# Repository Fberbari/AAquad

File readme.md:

This is an implementation of a quadcopter filght computer running baremetal on an atmega 328pb chip that takes input a standard hobby receiver and outputs pwm to esc's.

These directories contain the full firmware and the pcb design + gerber files.

As of right now, the system produces desirable results and has passed some basic functionality tests. 
I am currently waiting on a mechanical engineering student to finish designing the frame of the aircraft before further testing.

WORKING PRINCIPLE

	As of right now, the system reads input from the receiver via an interrupt based (asynchronous approach). This, because of the 50Hz pwm encoding that the receiver emits is by far the slowest process.

	Apart from this step, the rest of the processis synchronous and the loop goesas follows:

		1. The processor gathers data from the 2 on board sensors (accelerometer and gyroscope) via I2C.
		2. Using a modified version of the Kallman filter, the processor uses both pieces of data to determine the absolute position of the aircraft (with reference to gravity)
		3. A function gathers all the newest available data from the pilot and computes the pilots intention. (How should the aircraft bank and pitch and how strong should 		motor power be)
		4. A PID algorythim then uses the processed sensor data aswell, the processed pilot data and the previous cycle's data to compute 4 numbers that represent the 				percentage of full power that each motor should run at to best achieve the pilot's wishes
		5. Those numbers are encodedinto values that the pwm chip can understand and sent to it via I2C.
		6. The process repeats

PURPOSE

	The purose of this project was to familiarize myself with the basics of avr architecture, firmware design flow, communications between chips (I2C), pcb design flow etc.
	It was also a way to enter the world of embedded design in aviation. 

I (Anthony Berbari) AM SOLELY RESPONSIBLE FOR ALL THE FIRMWARE AND HARDWARE DESIGN DONE ON THIS PROJECT.

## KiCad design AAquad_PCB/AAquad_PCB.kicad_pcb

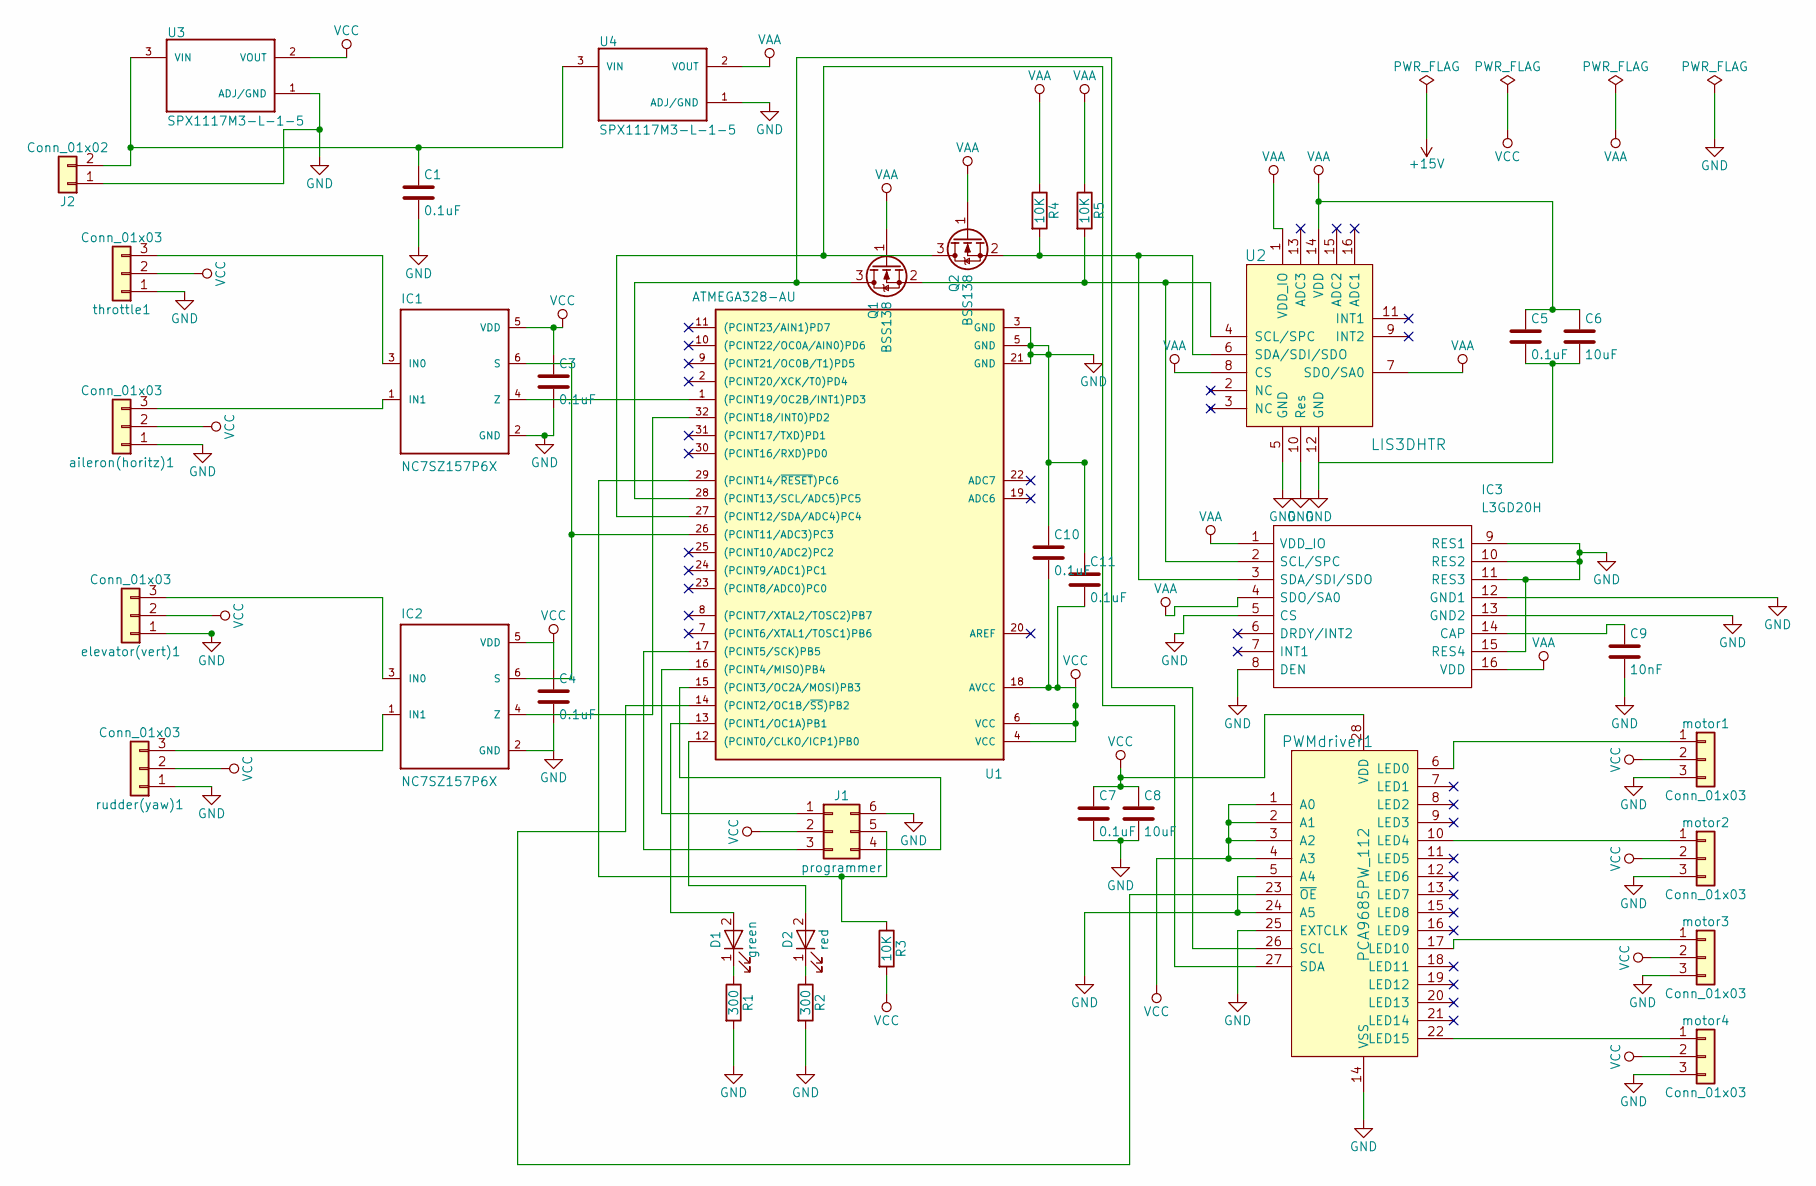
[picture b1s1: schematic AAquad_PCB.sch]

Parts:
C1, C3, C4, C5, C7, C10, C11: 0.1uF; C_0805_HandSoldering
C6, C8: 10uF; C_0805_HandSoldering
C9: 10nF; C_0805_HandSoldering
D1: green; LED_0805_HandSoldering
D2: red; LED_0805_HandSoldering
IC1, IC2: NC7SZ157P6X; SOT65P210X110-6N
IC3: L3GD20H; LGA(3X3X1.0-16L); Manufacturer_Part_Number L3GD20H
J1: programmer; Pin_Header_Angled_2x03_Pitch2.54mm
J2: Conn_01x02; Pin_Header_Angled_1x02_Pitch2.54mm
PWMdriver1: PCA9685PW_112; TSSOP-28_W4.40mm; MPN PCA9685PW,112; Digi-Key_PN 568-8366-5-ND
Q1, Q2: BSS138; SOT-23
R1, R2: 300; R_0805_HandSoldering
R3, R4, R5: 10K; R_0805_HandSoldering
U1: ATMEGA328-AU; TQFP-32_7x7mm_Pitch0.8mm
U2: LIS3DHTR; VFLGA-16_3x3mm; MPN LIS3DHTR; Digi-Key_PN 497-10613-1-ND
U3, U4: SPX1117M3-L-1-5; SOT230P700X180-3N
aileron(horitz)1: Conn_01x03; Pin_Header_Angled_1x03_Pitch2.54mm
elevator(vert)1: Conn_01x03; Pin_Header_Angled_1x03_Pitch2.54mm
motor1, motor2, motor3, motor4: Conn_01x03; Pin_Header_Angled_1x03_Pitch2.54mm
rudder(yaw)1: Conn_01x03; Pin_Header_Angled_1x03_Pitch2.54mm
throttle1: Conn_01x03; Pin_Header_Angled_1x03_Pitch2.54mm

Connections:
GND: C1.2, C3.2, C4.2, C5.2, C6.2, C7.2, C8.2, C9.2, C10.1, C11.1, IC1.2 (GND), IC2.2 (GND), IC3.5 (CS), IC3.8 (DEN), IC3.9 (RES1), IC3.10 (RES2), IC3.11 (RES3), IC3.12 (GND1), IC3.13 (GND2), IC3.15 (RES4), J1.6, J2.1, PWMdriver1.5 (A4), PWMdriver1.14 (VSS), PWMdriver1.24 (A5), PWMdriver1.25 (EXTCLK), R1.2, R2.2, U1.3 (GND), U1.5 (GND), U1.21 (GND), U2.5 (GND), U2.10 (Res), U2.12 (GND), U3.1 (ADJ/GND), U4.1 (ADJ/GND), aileron(horitz)1.1, elevator(vert)1.1, motor1.3, motor2.3, motor3.3, motor4.3, rudder(yaw)1.1, throttle1.1
unnamed: C1.1, J2.2, U3.3 (VIN), U4.3 (VIN)
unnamed: C9.1, IC3.14 (CAP)
unnamed: D1.1 (K), R1.1
unnamed: D1.2 (A), U1.13 ((PCINT1/OC1A)PB1)
unnamed: D2.1 (K), R2.1
unnamed: D2.2 (A), U1.12 ((PCINT0/CLKO/ICP1)PB0)
unnamed: IC1.1 (IN1), aileron(horitz)1.3
unnamed: IC1.3 (IN0), throttle1.3
unnamed: IC1.4 (Z), U1.1 ((PCINT19/OC2B/INT1)PD3)
unnamed: IC1.6 (S), IC2.6 (S), U1.26 ((PCINT11/ADC3)PC3)
unnamed: IC2.1 (IN1), rudder(yaw)1.3
unnamed: IC2.3 (IN0), elevator(vert)1.3
unnamed: IC2.4 (Z), U1.32 ((PCINT18/INT0)PD2)
unnamed: IC3.2 (SCL/SPC), Q1.2 (S), R5.2, U2.4 (SCL/SPC)
unnamed: IC3.3 (SDA/SDI/SDO), Q2.2 (S), R4.2, U2.6 (SDA/SDI/SDO)
unnamed: J1.1, U1.16 ((PCINT4/MISO)PB4)
unnamed: J1.3, U1.17 ((PCINT5/SCK)PB5)
unnamed: J1.4, U1.15 ((PCINT3/OC2A/MOSI)PB3)
unnamed: J1.5, R3.1, U1.29 ((PCINT14/~RESET~)PC6)
unnamed: PWMdriver1.6 (LED0), motor1.1
unnamed: PWMdriver1.10 (LED4), motor2.1
unnamed: PWMdriver1.17 (LED10), motor3.1
unnamed: PWMdriver1.22 (LED15), motor4.1
unnamed: PWMdriver1.23 (~OE), U1.14 ((PCINT2/OC1B/~SS~)PB2)
unnamed: PWMdriver1.26 (SCL), Q1.3 (D), U1.28 ((PCINT13/SCL/ADC5)PC5)
unnamed: PWMdriver1.27 (SDA), Q2.3 (D), U1.27 ((PCINT12/SDA/ADC4)PC4)
VAA: C5.1, C6.1, IC3.1 (VDD_IO), IC3.4 (SDO/SA0), IC3.16 (VDD), Q1.1 (G), Q2.1 (G), R4.1, R5.1, U2.1 (VDD_IO), U2.7 (SDO/SA0), U2.8 (CS), U2.14 (VDD), U4.2 (VOUT)
VCC: C3.1, C4.1, C7.1, C8.1, C10.2, C11.2, IC1.5 (VDD), IC2.5 (VDD), J1.2, PWMdriver1.1 (A0), PWMdriver1.2 (A1), PWMdriver1.3 (A2), PWMdriver1.4 (A3), PWMdriver1.28 (VDD), R3.2, U1.4 (VCC), U1.6 (VCC), U1.18 (AVCC), U3.2 (VOUT), aileron(horitz)1.2, elevator(vert)1.2, motor1.2, motor2.2, motor3.2, motor4.2, rudder(yaw)1.2, throttle1.2

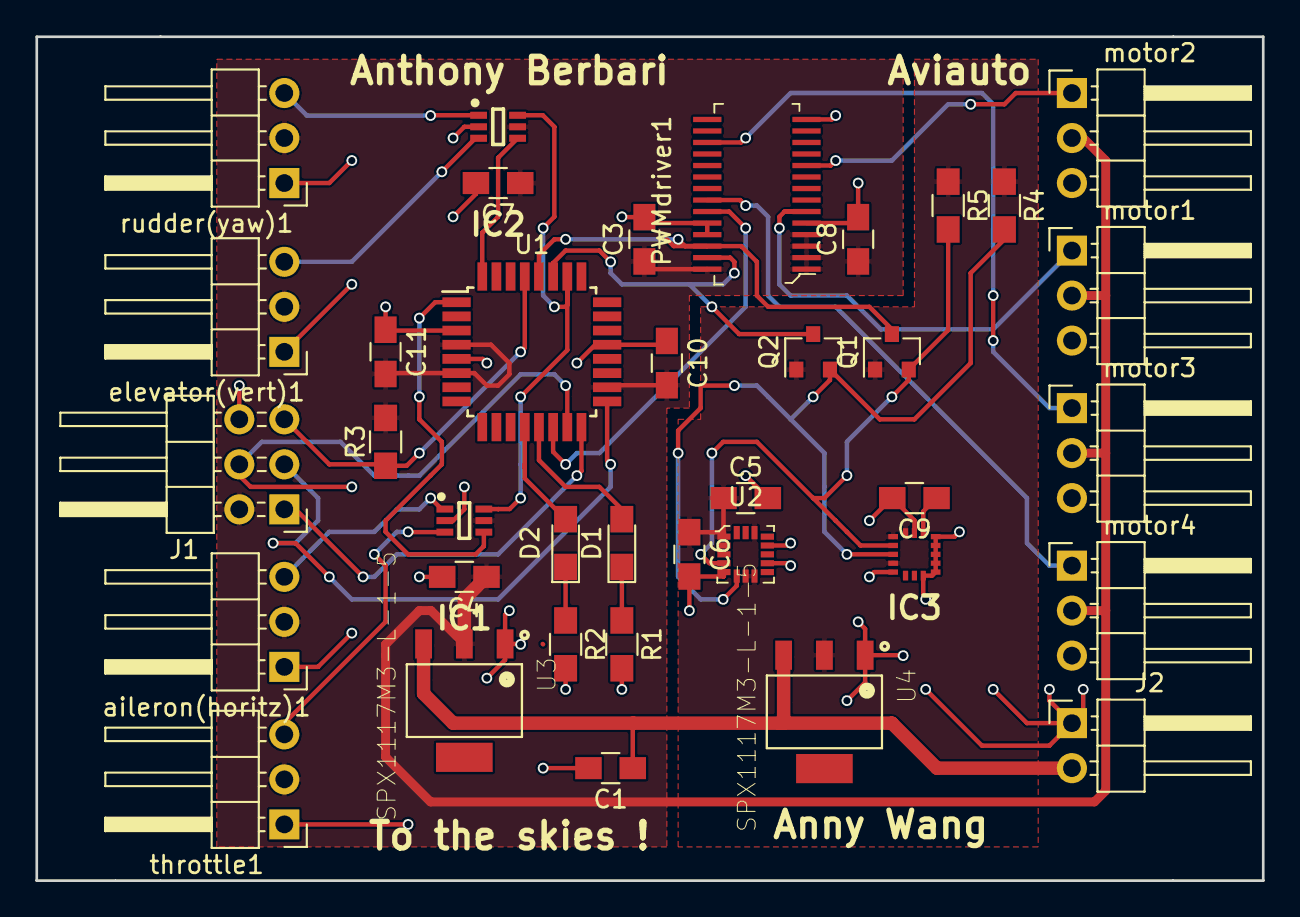
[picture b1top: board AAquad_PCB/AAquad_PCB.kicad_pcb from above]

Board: 2 copper layers, 69.2 x 47.6 mm, 37 parts (0 on the bottom side), 29 nets.

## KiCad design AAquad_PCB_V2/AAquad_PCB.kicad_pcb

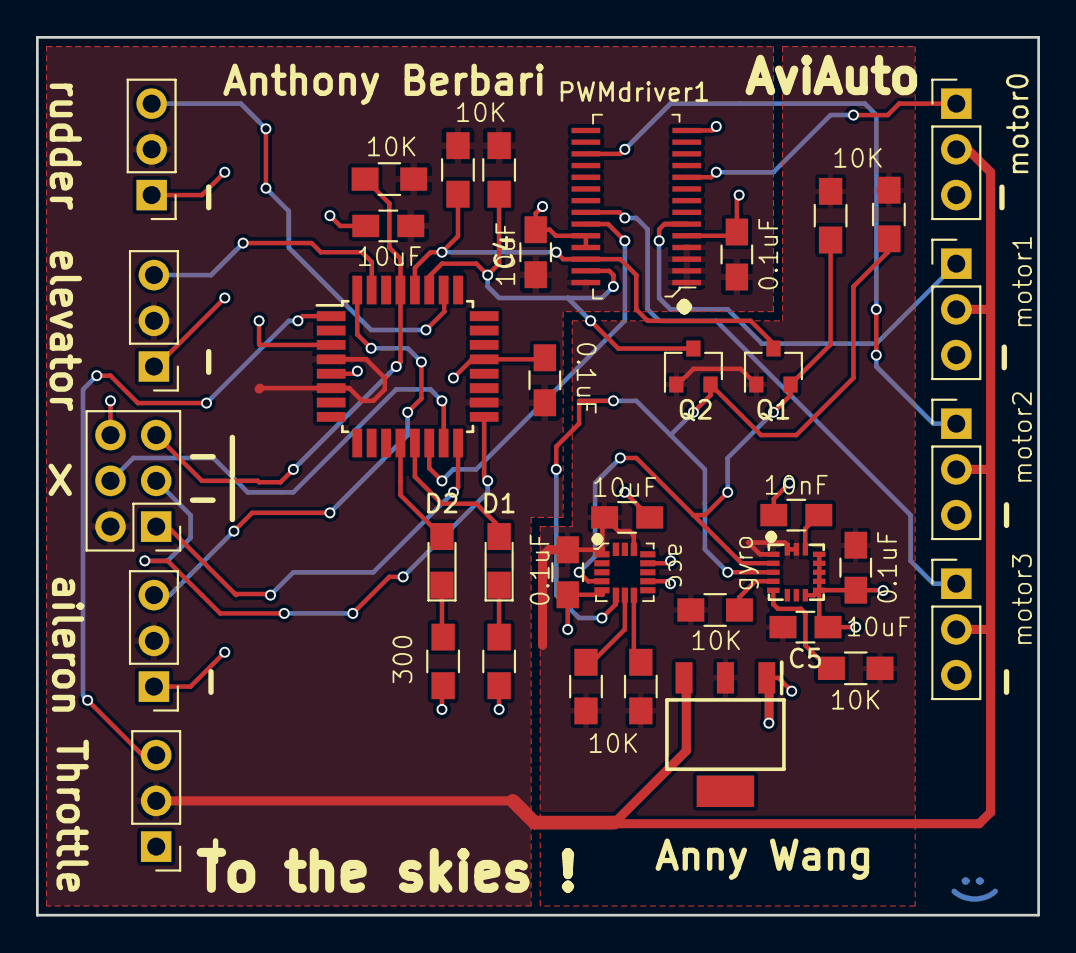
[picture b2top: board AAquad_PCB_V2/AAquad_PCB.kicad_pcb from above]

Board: 2 copper layers, 55.6 x 48.8 mm, 38 parts (0 on the bottom side), 29 nets.

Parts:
C1, C3, C6, C7: 0.1uF; C_0805_HandSoldering
C2, C4, C8: 10uF; C_0805_HandSoldering
C5: 10u; C_0805_HandSoldering
C9: 10nF; C_0805_HandSoldering
D1: green; LED_0805_HandSoldering
D2: red; LED_0805_HandSoldering
IC1: L3GD20H; L3gd20h
J1: programmer; Pin_Header_Straight_2x03_Pitch2.54mm
PS1: SPX1117M3-L-5-0_TR; SOT230P700X170-4N
PWMdriver1: PCA9685PW_112; TSSOP-28_W4.40mm
Q1, Q2: BSS138; SOT-23
R1, R2, R5, R6, R7, R8, R9, R10, R11: 10K; R_0805_HandSoldering
R3, R4: 300; R_0805_HandSoldering
U1: ATMEGA328-AU; TQFP-32_7x7mm_Pitch0.8mm
U2: LIS3DHTR; Lis3dh
aileron1: Conn_01x03; Pin_Header_Straight_1x03_Pitch2.54mm
elevator1: Conn_01x03; Pin_Header_Straight_1x03_Pitch2.54mm
motor1, motor2, motor3, motor4: Conn_01x03; Pin_Header_Straight_1x03_Pitch2.54mm
rudder1: Conn_01x03; Pin_Header_Straight_1x03_Pitch2.54mm
throttle1: Conn_01x03; Pin_Header_Straight_1x03_Pitch2.54mm

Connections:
GND: C1.1, C2.1, C3.2, C4.2, C5.1, C6.2, C7.2, C8.2, C9.2, IC1.8, IC1.9, IC1.10, IC1.11, IC1.12, IC1.13, J1.6, PS1.1, PWMdriver1.5, PWMdriver1.14, PWMdriver1.24, PWMdriver1.25, R3.2, R4.2, U1.3, U1.5, U1.21, U2.5, U2.10, U2.12, aileron1.1, elevator1.1, motor1.3, motor2.3, motor3.3, motor4.3, rudder1.1, throttle1.1
unnamed: C9.1, IC1.14
unnamed: D1.1, R3.1
unnamed: D1.2, U1.13
unnamed: D2.1, R4.1
unnamed: D2.2, U1.12
unnamed: IC1.2, Q1.2, R7.2, U2.4
unnamed: IC1.3, Q2.2, R6.2, U2.6
unnamed: IC1.4, R8.1
unnamed: IC1.5, R10.1
unnamed: J1.1, U1.16
unnamed: J1.3, U1.17
unnamed: J1.4, U1.15
unnamed: J1.5, R5.1, U1.29
unnamed: PWMdriver1.6, motor1.1
unnamed: PWMdriver1.10, motor2.1
unnamed: PWMdriver1.17, motor3.1
unnamed: PWMdriver1.22, motor4.1
unnamed: PWMdriver1.23, U1.14
unnamed: PWMdriver1.26, Q1.3, R2.1, U1.28
unnamed: PWMdriver1.27, Q2.3, R1.1, U1.27
unnamed: R9.1, U2.8
unnamed: R11.2, U2.7
unnamed: U1.1, throttle1.3
unnamed: U1.26, rudder1.3
unnamed: U1.31, elevator1.3
unnamed: U1.32, aileron1.3
VAA: C5.2, C6.1, C7.1, C8.1, IC1.1, IC1.15, IC1.16, PS1.2, Q1.1, Q2.1, R6.1, R7.1, R8.2, R9.2, R10.2, R11.1, U2.1, U2.14
VCC: C1.2, C2.2, C3.1, C4.1, J1.2, PS1.3, PWMdriver1.1, PWMdriver1.2, PWMdriver1.3, PWMdriver1.4, PWMdriver1.28, R1.2, R2.2, R5.2, U1.4, U1.6, U1.18, aileron1.2, elevator1.2, motor1.2, motor2.2, motor3.2, motor4.2, rudder1.2, throttle1.2

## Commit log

2018-06-14 added a readme.d
2018-06-18 added a list of necessary hardware
2018-06-26 ignore this commit
2018-07-15 added cart
2018-07-18 built the mux timer init function
2018-07-19 added a few functions
2018-07-19 added skeleton for math stuff
2018-07-29 many fixes and changes
2018-07-31 fixed pwm read
2018-08-01 fixed pwm read and fixed timer controll
2018-08-03 interfacing with PWM chip
2018-08-05 ignored atmel studio
2018-08-05 removedread function
2018-08-06 ignored atmelstudio file
2018-08-06 began to work on the translating motors branch
2018-08-06 fixed translate_motors_function
2018-08-07 successfull read and processing of PWM on ext_int0
2018-08-22 built PCB revision 2
2018-08-22 added accelerometer functon
2018-08-24 creation of gyro_init and advances on interrupts in main
2018-08-24 ignored Debug file
2018-08-25 began converting to c++
2018-08-27 sensor data processing
2018-08-27 began work on more accurate angle calculator
2018-08-27 finished first iteration ofsensor class
2018-08-28 installed and updated the PID class
2018-08-28 ignored pointless files
2018-09-01 working on PID class and integration with the whole app
2018-09-03 few smallfixes
2018-09-03 long poll preperly reading pwm
2018-09-03 pwm read from interrupts with wonderfull precision
2018-09-03 sameas previous
2018-09-03 properly and accurately reading pilot pwm on ext int 0
2018-09-03 succesfull conversion of throttle power to percentage
2018-09-05 properly reading all channels
2018-09-05 conversion of pilot data to appropriate angle achieved
2018-09-05 properly communicating with acc and gyro
2018-09-05 adjusted acc bit rate, acc readouts now compatible with the math
2018-09-06 acc + gyro data successfully combined to report angle
2018-09-06 PID algorythym functioning properly
2018-09-10 built proper PID algo
2018-09-11 pwm chip fixed !
2018-09-11 cleaned up
2018-09-11 cleaning up
2018-09-11 integration work
2018-09-12 all systems work roughly
2018-09-12 improved filtering
2018-09-12 more noise cleared
2018-09-13 ignored some directories
2018-09-13 ignored directories
2018-09-17 updated readme and added documentation
2018-09-17 added more documentation and cleaned directories
2018-09-17 fixed typos
2018-10-01 added pictures
2018-10-12 updated classes to make use of inheritance
2018-10-15 ignored files and rearranged directories
2018-10-16 upgraded to use bullet proof pid class
2018-10-27 called pid from timer interrupt
